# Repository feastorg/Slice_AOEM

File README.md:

# Atlas Sci OEM

Altas Scientific OEM component Slice for BREAD (pH, DO, EC, ORP).

## Introduction

[Short introduction on the project.]

## Usage

[Explain how to use the project. Include examples and screenshots if applicable.]

## Documentation

Please refer to the [docs](/docs) for more info.

---

<div align="center">
  
</div>

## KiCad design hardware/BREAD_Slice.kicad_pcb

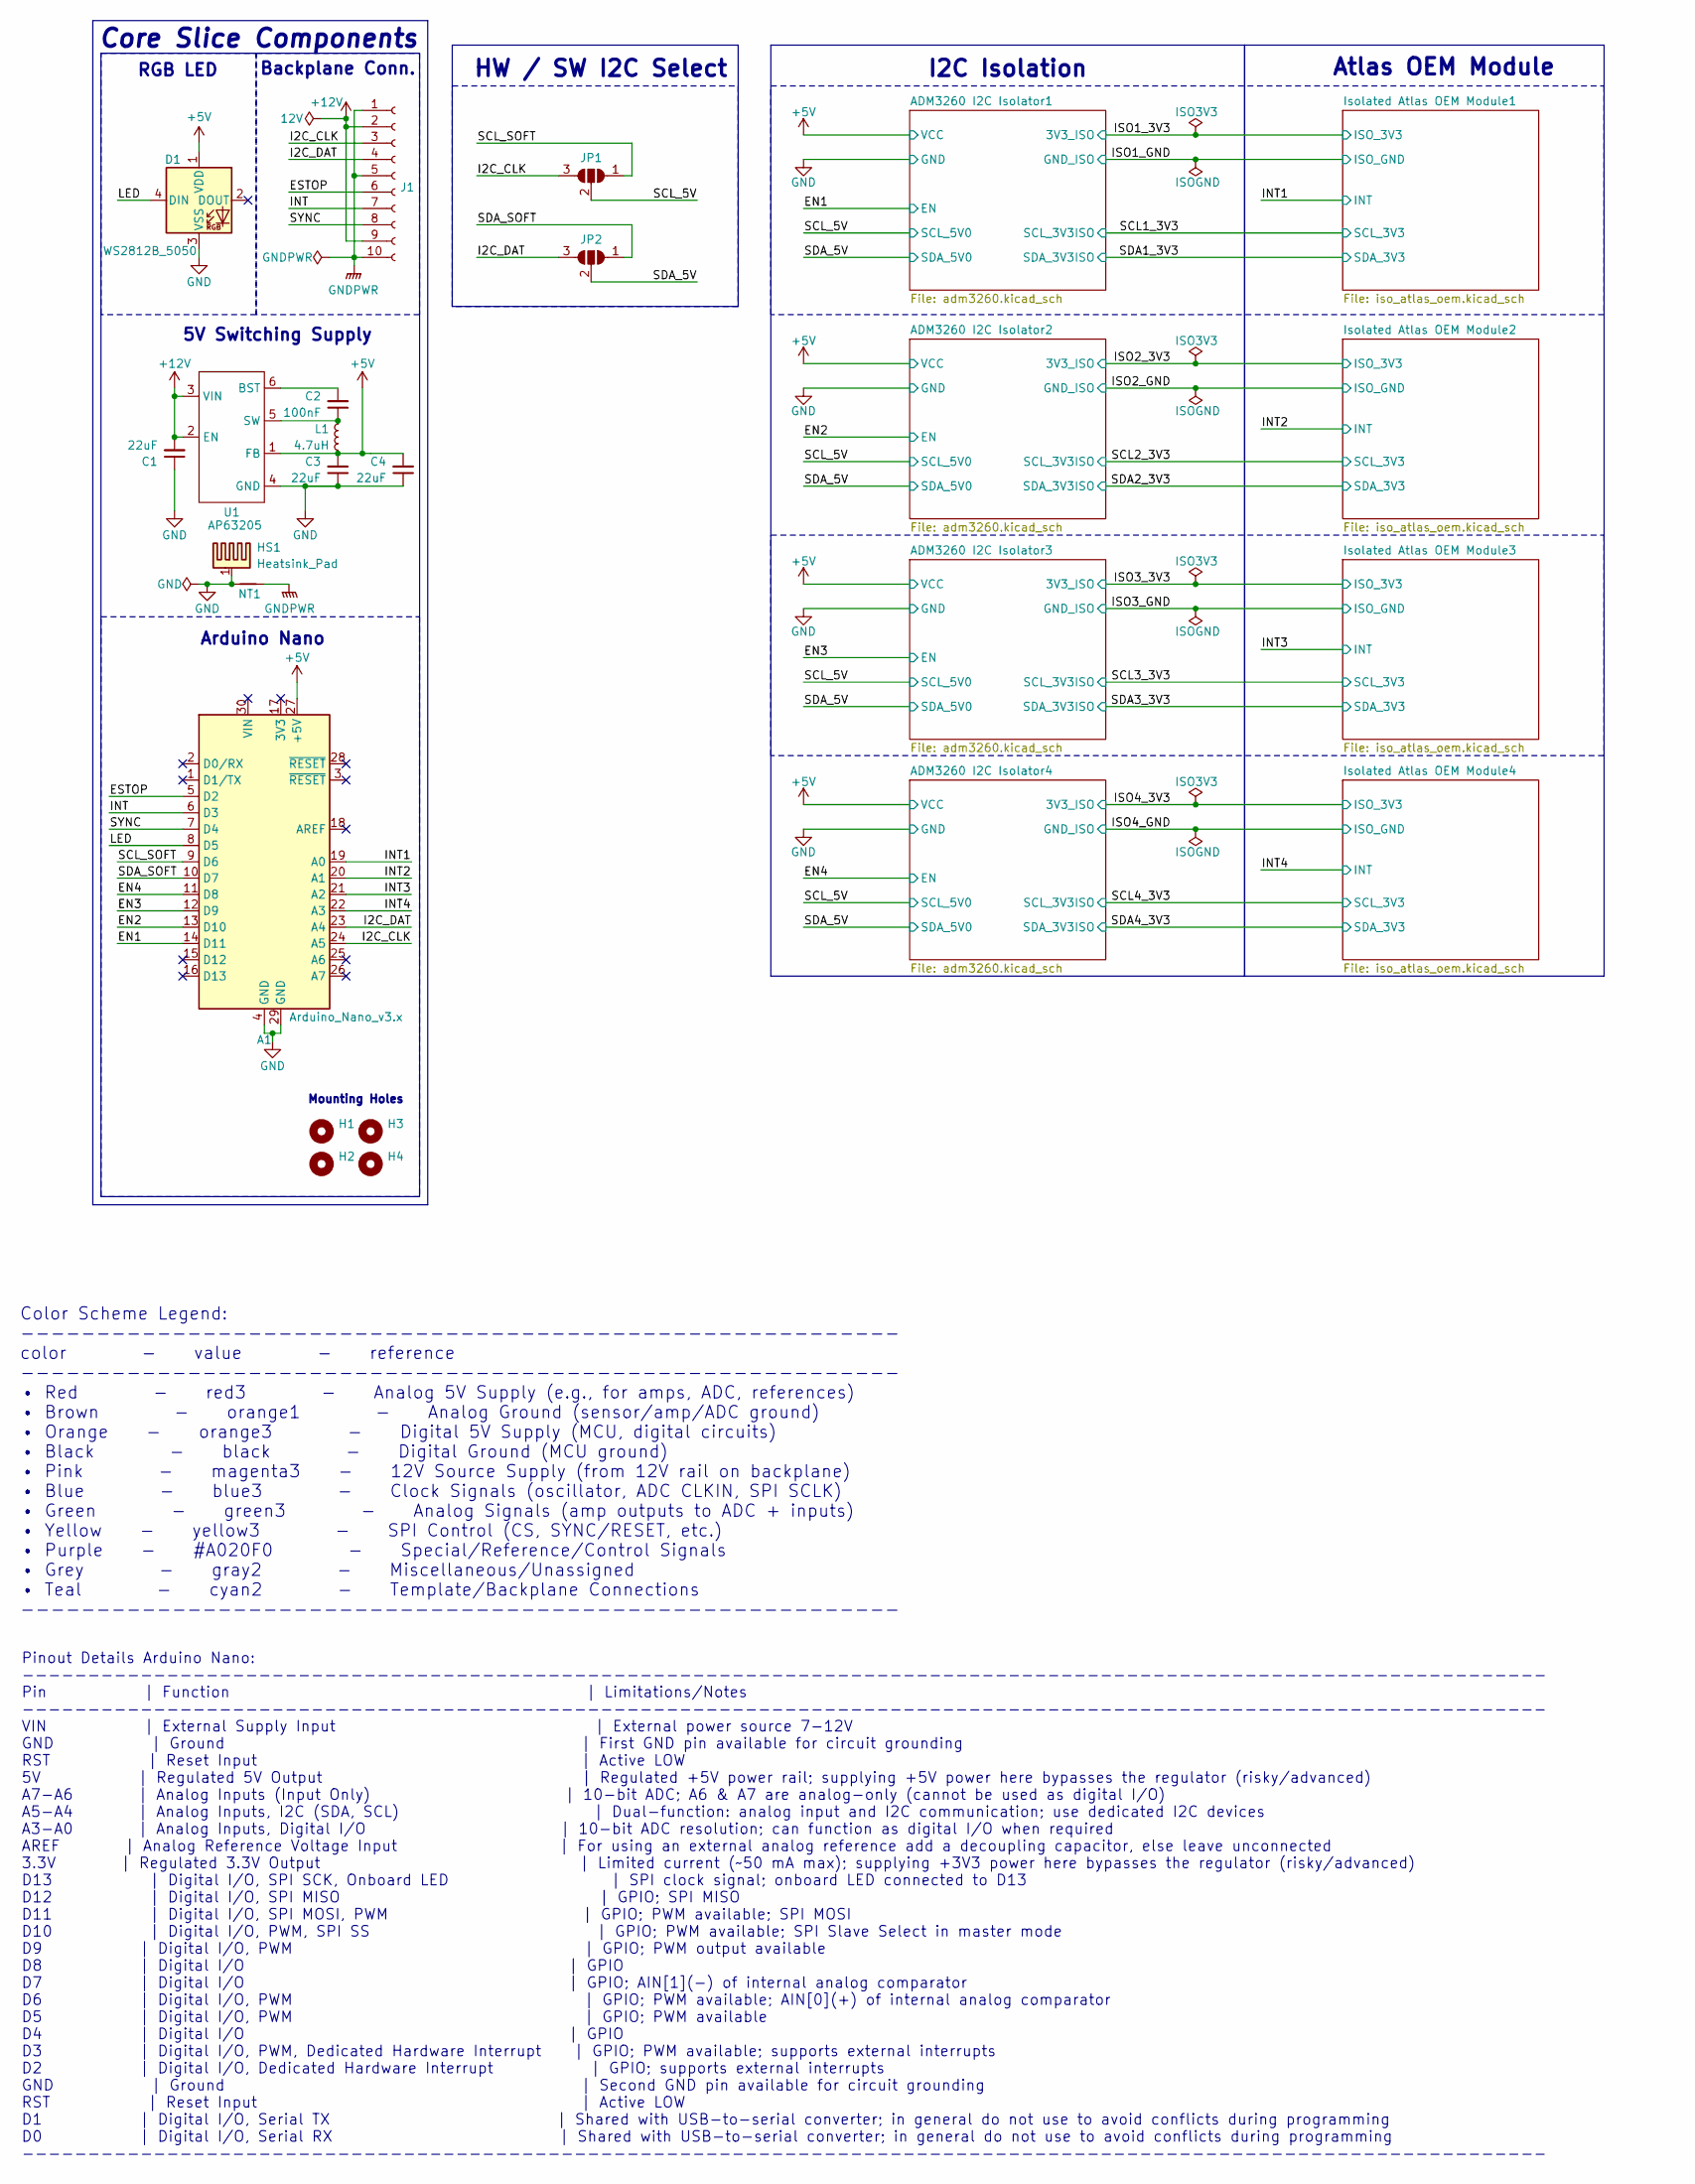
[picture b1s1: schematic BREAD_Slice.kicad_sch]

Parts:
A1: Arduino_Nano_v3.x; Arduino_Nano
C1, C3, C4: 22uF; C_1206_3216Metric
C2: 100nF; C_1206_3216Metric
D1: WS2812B_5050; WS2812-5050-4PIN
H1, H2, H3, H4: MountingHole; MountingHole_5mm
HS1: Heatsink_Pad; Thermal_Pad
J1: Conn_01x10_Female; PinSocket_1x10_P2.54mm_Horizontal
JP1, JP2: SolderJumper_3_Open; SolderJumper-3_P1.3mm_Open_RoundedPad1.0x1.5mm
L1: 4.7uH; L_1210_3225Metric
NT1: NetTie_2; NetTie-2_SMD_Pad2.0mm
U1: AP63205; SOIC_05WU-7_DIO

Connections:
+5V: A1.27 (+5V), C3.2, C4.2, D1.1 (VDD), L1.2, U1.1 (FB); also elsewhere on the board
+12V: C1.2, J1.2, J1.9, U1.2 (EN), U1.3 (VIN)
/EN1: A1.14 (D11); also elsewhere on the board
/EN2: A1.13 (D10); also elsewhere on the board
/EN3: A1.12 (D9); also elsewhere on the board
/EN4: A1.11 (D8); also elsewhere on the board
/ESTOP: A1.5 (D2), J1.6
/I2C_CLK: A1.24 (A5), J1.3, JP1.3 (B)
/I2C_DAT: A1.23 (A4), J1.4, JP2.3 (B)
/INT: A1.6 (D3), J1.7
/INT1: A1.19 (A0); also elsewhere on the board
/INT2: A1.20 (A1); also elsewhere on the board
/INT3: A1.21 (A2); also elsewhere on the board
/INT4: A1.22 (A3); also elsewhere on the board
/LED: A1.8 (D5), D1.4 (DIN)
/SCL_5V: JP1.2 (C); also elsewhere on the board
/SCL_SOFT: A1.9 (D6), JP1.1 (A)
/SDA_5V: JP2.2 (C); also elsewhere on the board
/SDA_SOFT: A1.10 (D7), JP2.1 (A)
/SYNC: A1.7 (D4), J1.8
GND: A1.4 (GND), A1.29 (GND), C1.1, C3.1, C4.1, D1.3 (VSS), HS1.1, NT1.1, U1.4 (GND); also elsewhere on the board
GNDPWR: J1.1, J1.5, J1.10, NT1.2
unnamed: C2.2, U1.6 (BST)
unnamed: C2.1, L1.1, U1.5 (SW)

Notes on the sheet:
5V Switching Supply
Atlas OEM Module
Pinout Details Arduino Nano: -------------------------------------------------------------------------------------------------------------------- Pin | Function | Limitations/Notes -------------------------------------------------------------------------------------------------------------------- V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
RGB LED
Color Scheme Legend: ---------------------------------------------------------- color - value - reference ---------------------------------------------------------- • Red - red3 - Analog 5V Supply (e.g., for amps, ADC, references) • Brown - orange1 - Analog Ground (sensor/amp/ADC ground) • Orange -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
HW / SW I2C Select
I2C Isolation
Core Slice Components
Arduino Nano
Mounting Holes
Backplane Conn.

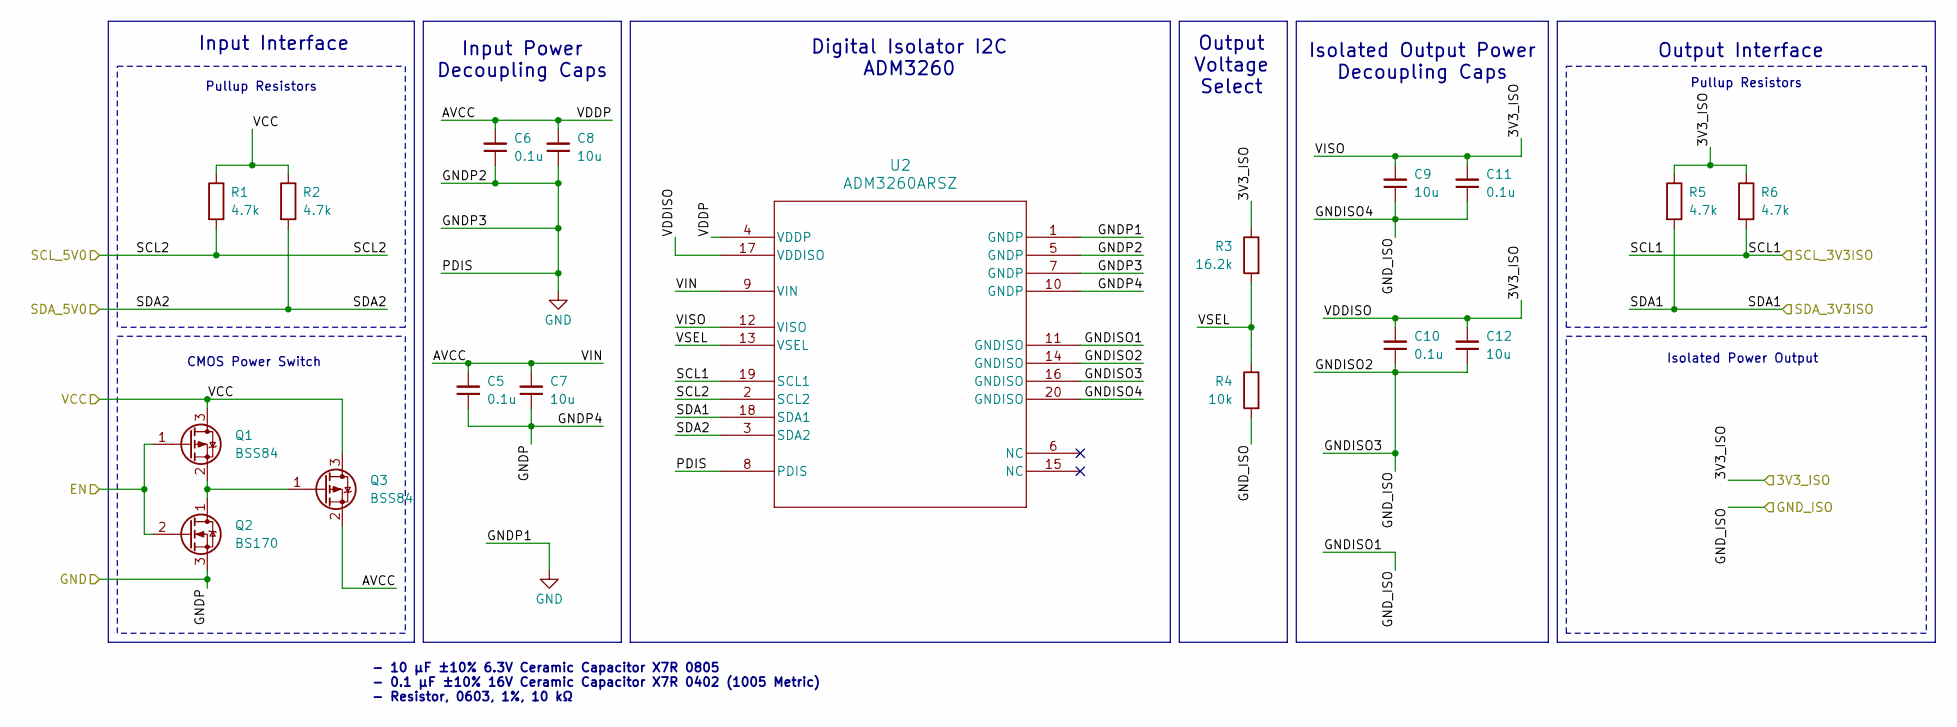
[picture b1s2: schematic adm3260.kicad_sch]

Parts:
C5, C6, C10, C11: 0.1u; C_0603_1608Metric_Pad1.08x0.95mm_HandSolder
C7, C8, C9, C12: 10u; C_0805_2012Metric_Pad1.18x1.45mm_HandSolder
Q1, Q3: BSS84; SOT-23
Q2: BS170; SOT-23
R1, R2, R5, R6: 4.7k; R_0603_1608Metric_Pad0.98x0.95mm_HandSolder
R3: 16.2k; R_0603_1608Metric_Pad0.98x0.95mm_HandSolder
R4: 10k; R_0603_1608Metric_Pad0.98x0.95mm_HandSolder
U2: ADM3260ARSZ; RS_20_ADI

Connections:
+5V: Q1.3 (D), Q3.3 (D), R1.1, R2.1; also elsewhere on the board
/ADM3260 I2C Isolator1/AVCC: C5.2, C6.2, C7.2, C8.2, Q3.2 (S), U2.4 (VDDP), U2.9 (VIN)
/ADM3260 I2C Isolator1/VSEL: R3.2, R4.1, U2.13 (VSEL)
/EN1: Q1.1 (G), Q2.2 (G); also elsewhere on the board
/ISO1_3V3: C9.2, C10.2, C11.2, C12.2, R3.1, R5.1, R6.1, U2.12 (VISO), U2.17 (VDDISO); also elsewhere on the board
/ISO1_GND: C9.1, C10.1, C11.1, C12.1, R4.2, U2.11 (GNDISO), U2.14 (GNDISO), U2.16 (GNDISO), U2.20 (GNDISO); also elsewhere on the board
/SCL1_3V3: R6.2, U2.19 (SCL1); also elsewhere on the board
/SCL_5V: R1.2, U2.2 (SCL2); also elsewhere on the board
/SDA1_3V3: R5.2, U2.18 (SDA1); also elsewhere on the board
/SDA_5V: R2.2, U2.3 (SDA2); also elsewhere on the board
GND: C5.1, C6.1, C7.1, C8.1, Q2.3 (S), U2.1 (GNDP), U2.5 (GNDP), U2.7 (GNDP), U2.8 (PDIS), U2.10 (GNDP); also elsewhere on the board
unnamed: Q1.2 (S), Q2.1 (D), Q3.1 (G)

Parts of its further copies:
C13, C14, C18, C19, C21, C22, C26, C27, C29, C30, C34, C35: 0.1u; C_0603_1608Metric_Pad1.08x0.95mm_HandSolder
C15, C16, C17, C20, C23, C24, C25, C28, C31, C32, C33, C36: 10u; C_0805_2012Metric_Pad1.18x1.45mm_HandSolder
Q4, Q6, Q7, Q9, Q10, Q12: BSS84; SOT-23
Q5, Q8, Q11: BS170; SOT-23
R7, R8, R11, R12, R13, R14, R17, R18, R19, R20, R23, R24: 4.7k; R_0603_1608Metric_Pad0.98x0.95mm_HandSolder
R9, R15, R21: 16.2k; R_0603_1608Metric_Pad0.98x0.95mm_HandSolder
R10, R16, R22: 10k; R_0603_1608Metric_Pad0.98x0.95mm_HandSolder
U4, U6, U8: ADM3260ARSZ; RS_20_ADI

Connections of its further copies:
+5V: Q4.3 (D), Q6.3 (D), Q7.3 (D), Q9.3 (D), Q10.3 (D), Q12.3 (D), R7.1, R8.1, R13.1, R14.1, R19.1, R20.1; also elsewhere on the board
/ADM3260 I2C Isolator2/AVCC: C13.2, C14.2, C15.2, C16.2, Q6.2 (S), U4.4 (VDDP), U4.9 (VIN)
/ADM3260 I2C Isolator2/VSEL: R9.2, R10.1, U4.13 (VSEL)
/ADM3260 I2C Isolator3/AVCC: C21.2, C22.2, C23.2, C24.2, Q9.2 (S), U6.4 (VDDP), U6.9 (VIN)
/ADM3260 I2C Isolator3/VSEL: R15.2, R16.1, U6.13 (VSEL)
/ADM3260 I2C Isolator4/AVCC: C29.2, C30.2, C31.2, C32.2, Q12.2 (S), U8.4 (VDDP), U8.9 (VIN)
/ADM3260 I2C Isolator4/VSEL: R21.2, R22.1, U8.13 (VSEL)
/EN2: Q4.1 (G), Q5.2 (G); also elsewhere on the board
/EN3: Q7.1 (G), Q8.2 (G); also elsewhere on the board
/EN4: Q10.1 (G), Q11.2 (G); also elsewhere on the board
/ISO2_3V3: C17.2, C18.2, C19.2, C20.2, R9.1, R11.1, R12.1, U4.12 (VISO), U4.17 (VDDISO); also elsewhere on the board
/ISO2_GND: C17.1, C18.1, C19.1, C20.1, R10.2, U4.11 (GNDISO), U4.14 (GNDISO), U4.16 (GNDISO), U4.20 (GNDISO); also elsewhere on the board
/ISO3_3V3: C25.2, C26.2, C27.2, C28.2, R15.1, R17.1, R18.1, U6.12 (VISO), U6.17 (VDDISO); also elsewhere on the board
/ISO3_GND: C25.1, C26.1, C27.1, C28.1, R16.2, U6.11 (GNDISO), U6.14 (GNDISO), U6.16 (GNDISO), U6.20 (GNDISO); also elsewhere on the board
/ISO4_3V3: C33.2, C34.2, C35.2, C36.2, R21.1, R23.1, R24.1, U8.12 (VISO), U8.17 (VDDISO); also elsewhere on the board
/ISO4_GND: C33.1, C34.1, C35.1, C36.1, R22.2, U8.11 (GNDISO), U8.14 (GNDISO), U8.16 (GNDISO), U8.20 (GNDISO); also elsewhere on the board
/SCL2_3V3: R12.2, U4.19 (SCL1); also elsewhere on the board
/SCL3_3V3: R18.2, U6.19 (SCL1); also elsewhere on the board
/SCL4_3V3: R24.2, U8.19 (SCL1); also elsewhere on the board
/SCL_5V: R7.2, R13.2, R19.2, U4.2 (SCL2), U6.2 (SCL2), U8.2 (SCL2); also elsewhere on the board
/SDA2_3V3: R11.2, U4.18 (SDA1); also elsewhere on the board
/SDA3_3V3: R17.2, U6.18 (SDA1); also elsewhere on the board
/SDA4_3V3: R23.2, U8.18 (SDA1); also elsewhere on the board
/SDA_5V: R8.2, R14.2, R20.2, U4.3 (SDA2), U6.3 (SDA2), U8.3 (SDA2); also elsewhere on the board
GND: C13.1, C14.1, C15.1, C16.1, C21.1, C22.1, C23.1, C24.1, C29.1, C30.1, C31.1, C32.1, Q5.3 (S), Q8.3 (S), Q11.3 (S), U4.1 (GNDP), U4.5 (GNDP), U4.7 (GNDP), U4.8 (PDIS), U4.10 (GNDP), U6.1 (GNDP), U6.5 (GNDP), U6.7 (GNDP), U6.8 (PDIS), U6.10 (GNDP), U8.1 (GNDP), U8.5 (GNDP), U8.7 (GNDP), U8.8 (PDIS), U8.10 (GNDP); also elsewhere on the board
unnamed: Q4.2 (S), Q5.1 (D), Q6.1 (G)
unnamed: Q7.2 (S), Q8.1 (D), Q9.1 (G)
unnamed: Q10.2 (S), Q11.1 (D), Q12.1 (G)

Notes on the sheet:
Isolated Power Output
Output Interface
CMOS Power Switch
Pullup Resistors
- 10 µF ±10% 6.3V Ceramic Capacitor X7R 0805 - 0.1 µF ±10% 16V Ceramic Capacitor X7R 0402 (1005 Metric) - Resistor, 0603, 1%, 10 kΩ
Isolated Output Power Decoupling Caps
Input Interface
Output Voltage Select
Digital Isolator I2C ADM3260
Input Power Decoupling Caps

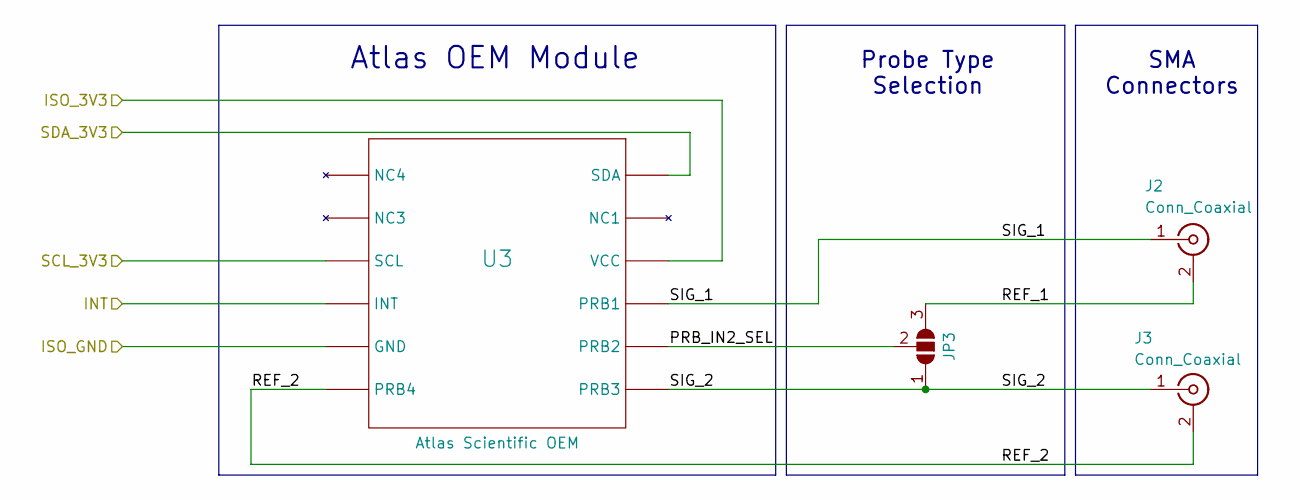
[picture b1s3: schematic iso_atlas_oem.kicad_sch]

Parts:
J2, J3: Conn_Coaxial; SMA_Molex_73251-1153_EdgeMount_Horizontal
JP3: SolderJumper_3_Open; SolderJumper-3_P1.3mm_Open_RoundedPad1.0x1.5mm
U3: Atlas Scientific OEM; Atlas_OEM

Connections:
/INT1: U3.P9 (INT); also elsewhere on the board
/ISO1_3V3: U3.P3 (VCC); also elsewhere on the board
/ISO1_GND: U3.P8 (GND); also elsewhere on the board
/Isolated Atlas OEM Module1/PRB_IN2_SEL: JP3.2 (C), U3.P5 (PRB2)
/Isolated Atlas OEM Module1/REF_1: J2.2 (Ext), JP3.3 (B)
/Isolated Atlas OEM Module1/REF_2: J3.2 (Ext), U3.P7 (PRB4)
/Isolated Atlas OEM Module1/SIG_1: J2.1 (In), U3.P4 (PRB1)
/Isolated Atlas OEM Module1/SIG_2: J3.1 (In), JP3.1 (A), U3.P6 (PRB3)
/SCL1_3V3: U3.P10 (SCL); also elsewhere on the board
/SDA1_3V3: U3.P1 (SDA); also elsewhere on the board

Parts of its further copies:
J4, J5, J6, J7, J8, J9: Conn_Coaxial; SMA_Molex_73251-1153_EdgeMount_Horizontal
JP4, JP5, JP6: SolderJumper_3_Open; SolderJumper-3_P1.3mm_Open_RoundedPad1.0x1.5mm
U5, U7, U9: Atlas Scientific OEM; Atlas_OEM

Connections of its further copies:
/INT2: U5.P9 (INT); also elsewhere on the board
/INT3: U7.P9 (INT); also elsewhere on the board
/INT4: U9.P9 (INT); also elsewhere on the board
/ISO2_3V3: U5.P3 (VCC); also elsewhere on the board
/ISO2_GND: U5.P8 (GND); also elsewhere on the board
/ISO3_3V3: U7.P3 (VCC); also elsewhere on the board
/ISO3_GND: U7.P8 (GND); also elsewhere on the board
/ISO4_3V3: U9.P3 (VCC); also elsewhere on the board
/ISO4_GND: U9.P8 (GND); also elsewhere on the board
/Isolated Atlas OEM Module2/PRB_IN2_SEL: JP4.2 (C), U5.P5 (PRB2)
/Isolated Atlas OEM Module2/REF_1: J4.2 (Ext), JP4.3 (B)
/Isolated Atlas OEM Module2/REF_2: J5.2 (Ext), U5.P7 (PRB4)
/Isolated Atlas OEM Module2/SIG_1: J4.1 (In), U5.P4 (PRB1)
/Isolated Atlas OEM Module2/SIG_2: J5.1 (In), JP4.1 (A), U5.P6 (PRB3)
/Isolated Atlas OEM Module3/PRB_IN2_SEL: JP5.2 (C), U7.P5 (PRB2)
/Isolated Atlas OEM Module3/REF_1: J6.2 (Ext), JP5.3 (B)
/Isolated Atlas OEM Module3/REF_2: J7.2 (Ext), U7.P7 (PRB4)
/Isolated Atlas OEM Module3/SIG_1: J6.1 (In), U7.P4 (PRB1)
/Isolated Atlas OEM Module3/SIG_2: J7.1 (In), JP5.1 (A), U7.P6 (PRB3)
/Isolated Atlas OEM Module4/PRB_IN2_SEL: JP6.2 (C), U9.P5 (PRB2)
/Isolated Atlas OEM Module4/REF_1: J8.2 (Ext), JP6.3 (B)
/Isolated Atlas OEM Module4/REF_2: J9.2 (Ext), U9.P7 (PRB4)
/Isolated Atlas OEM Module4/SIG_1: J8.1 (In), U9.P4 (PRB1)
/Isolated Atlas OEM Module4/SIG_2: J9.1 (In), JP6.1 (A), U9.P6 (PRB3)
/SCL2_3V3: U5.P10 (SCL); also elsewhere on the board
/SCL3_3V3: U7.P10 (SCL); also elsewhere on the board
/SCL4_3V3: U9.P10 (SCL); also elsewhere on the board
/SDA2_3V3: U5.P1 (SDA); also elsewhere on the board
/SDA3_3V3: U7.P1 (SDA); also elsewhere on the board
/SDA4_3V3: U9.P1 (SDA); also elsewhere on the board

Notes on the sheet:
SMA Connectors
Probe Type Selection
Atlas OEM Module

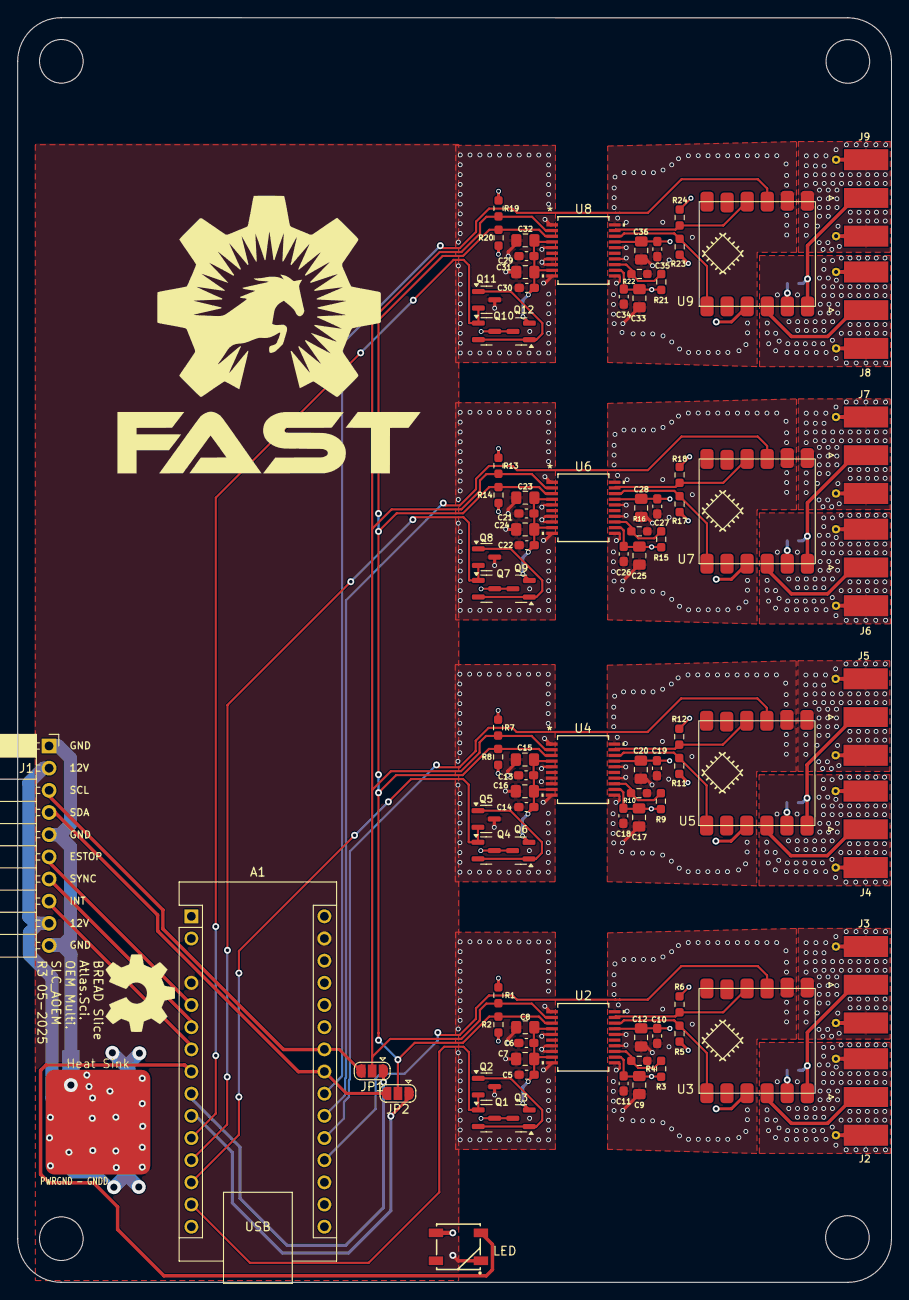
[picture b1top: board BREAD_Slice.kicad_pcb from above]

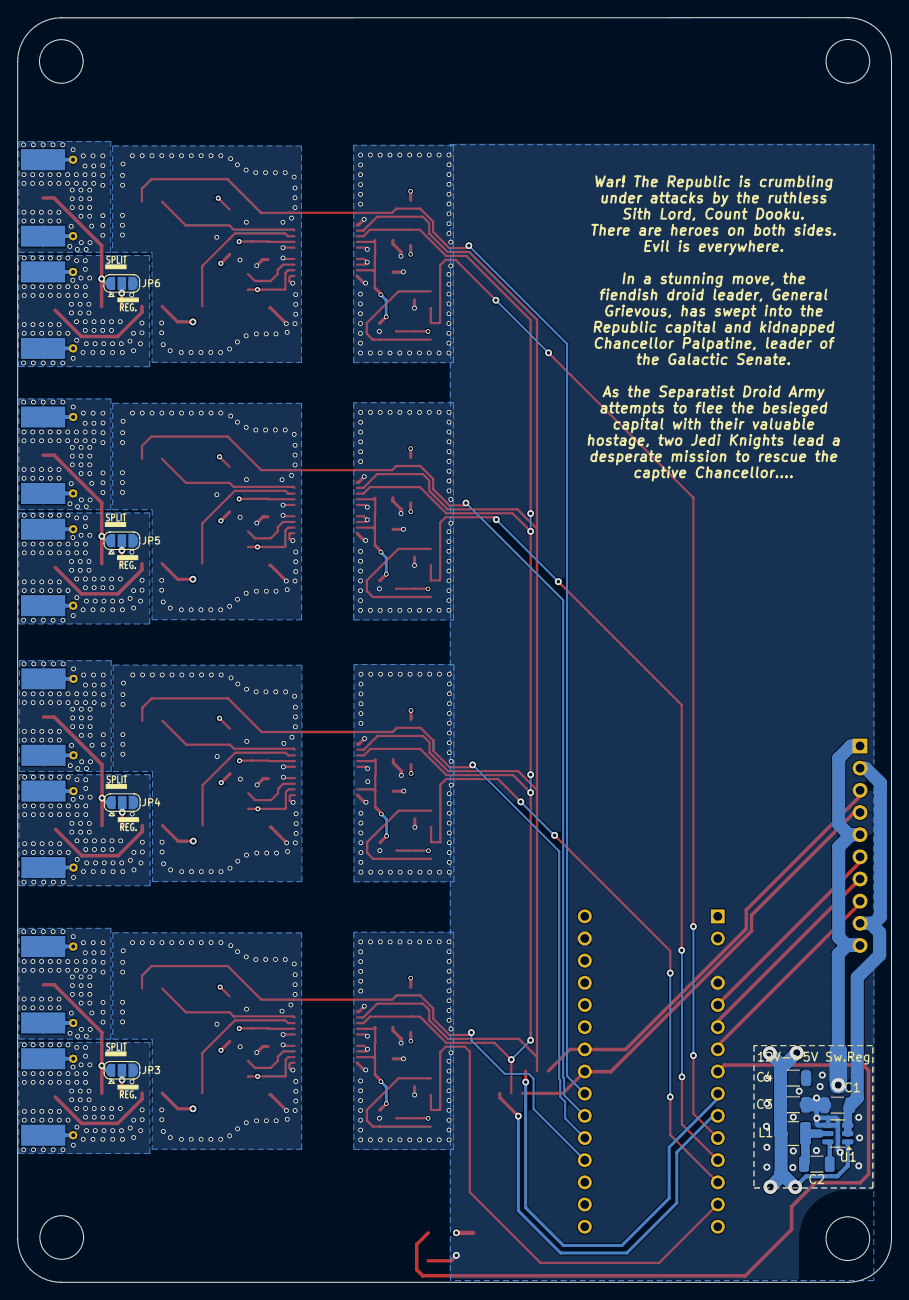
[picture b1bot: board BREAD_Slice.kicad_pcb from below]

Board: 4 copper layers, 100.1 x 144.9 mm, 105 parts (11 on the bottom side), 72 nets.

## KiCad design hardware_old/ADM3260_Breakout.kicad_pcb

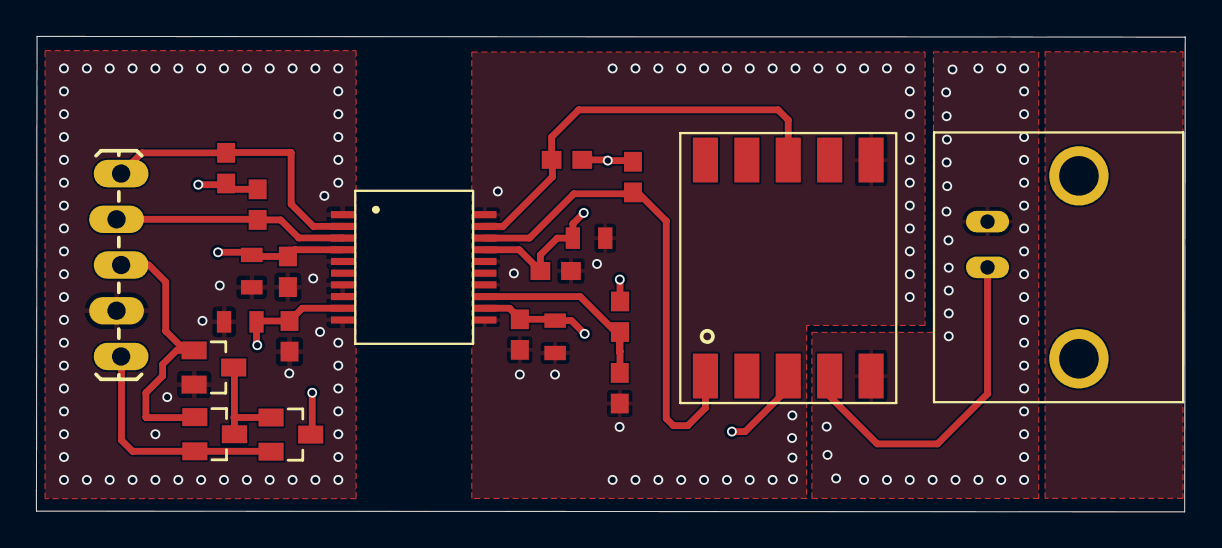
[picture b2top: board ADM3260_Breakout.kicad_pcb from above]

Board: 4 copper layers, 63.8 x 26.4 mm, 21 parts (0 on the bottom side), 14 nets.

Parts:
C1, C3, C6, C8: 10uF; 0805
C2, C4, C5, C7: 0.1uF; 0603
J1: 1X05_LOCK_LONGPADS
J2: BNCPTH; BNC
Q1, Q3: PMV32UP; SOT23
Q2: PMV16XN; SOT23
R1, R2, R3, R4: 4.7k; 0603
R5: 16.2k; 0603
R6: 10k; 0603
U1: ADM3260
U2: Atlas Scientific OEM pH or ORP; PHSENSOR

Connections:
3V3-ISO: C5.1, C6.1, C7.1, C8.1, R3.2, R4.2, R5.2, U1.P$12, U1.P$17, U2.P$3
AVCC: C1.1, C2.1, C3.1, C4.1, Q3.3, R1.2, R2.2, U1.P$4, U1.P$9
EN: J1.3, Q1.1, Q2.1
GND: C1.2, C2.2, C3.2, C4.2, J1.4, Q2.2, U1.P$1, U1.P$5, U1.P$7, U1.P$8, U1.P$10
GND-ISO: C5.2, C6.2, C7.2, C8.2, R6.1, U1.P$11, U1.P$14, U1.P$16, U1.P$20, U2.P$6
unnamed: R5.1, R6.2, U1.P$13
unnamed: Q1.3, Q2.3, Q3.1
PRB: J2.S, U2.P$4
PRBGND: J2.GND, U2.P$5
SCL1: R4.1, U1.P$19, U2.P$8
SCL2: J1.1, R1.1, U1.P$2
SDA1: R3.1, U1.P$18, U2.P$1
SDA2: J1.2, R2.1, U1.P$3
VCC: J1.5, Q1.2, Q3.2

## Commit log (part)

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2024-09-10 set repo
2025-04-15 schematic done, board needs replication for all 4 channels
2025-05-06 finalized pcb
2025-05-06 removed legacy folders
2025-05-06 removed bkups
2026-05-20 Add slice.yaml manifest (schema v1.0)
2026-05-20 Add KiBot/docs pipeline
2026-05-20 Update TODO with CI ERC findings
2026-05-27 expand gitignore to include backups, locks, and history autogenerated files
2026-05-27 !feat: upgrade to kicad 10
